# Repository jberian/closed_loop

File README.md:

Closed-Loop System for Type 1 diabetes
====

    This repository contains all the projects needed to build a 
    wearable closed-loop system for type 1 diabetes that uses a new
    algorithm to estimate the basal insulin needs of the patient and
    perform the control using temporary basal rates.

## Disclaimer

    This software and information is designed for educational purposes only 
    and should NEVER be used on real patients.
    
    This information is provided 'as is' and in no event shall the 
    provider be liable for any damages, including, without 
    limitation, damages resulting from lost data or lost profits or 
    revenue, the costs of recovering such data, the costs of substitute 
    data, claims by third parties or for other similar costs, or any 
    special, incidental, or consequential damages arising out of use or
    misuse of this data. The accuracy or reliability of the data is not 
    guaranteed or warranted in any way and the provider disclaim 
    liability of any kind whatsoever, including, without limitation, 
    liability for quality, performance, merchantability and fitness 
    for a particular purpose arising out of the use, or inability 
    to use the data. Information obtained via this software MUST
    NEVER BE USED to take medical decisions.

## [License - GPL V2](gpl-v2)
[gpl-2]: https://www.gnu.org/licenses/old-licenses/gpl-2.0.txt

    This program is free software: you can redistribute it and/or modify
    it under the terms of the GNU General Public License as published by
    the Free Software Foundation version 2 of the License.

    This program is distributed in the hope that it will be useful,
    but WITHOUT ANY WARRANTY; without even the implied warranty of
    MERCHANTABILITY or FITNESS FOR A PARTICULAR PURPOSE.  See the
    GNU General Public License for more details.

    You should have received a copy of the GNU General Public License
    along with this program.  If not, see <http://www.gnu.org/licenses/>.

## Contents

   This repository containts the following information in their corresponding
   folder:
   
1. **Demo** - Contains a time-lapse video of a demo system connected to Nightscout and controlling a patient's glycaemia.

2. **Firmware** - Contains the project files needed to compile the platform's CC1111 firmware using IAR Embedded Workbench (the trial version should be enough). The code for the CC2540 processor is not included since the project should be downloaded directly from TI's website.
   
3. **Platform** - Contains the information to build two different platforms: 
    1. *Prototype* - It's a PCB in which some commercial off-the-self boards can be soldered and provides the needed interconnections for the system.
    2. *Final* - Final version of the wearable system.
 
4. **Publications** - Publications related to this work.

5. **Simulation** - Contains a modified version of the [simglucose simulator](https://github.com/jxx123/simglucose) along with a controller that behaves like the "real" version of the controller.

6. **Uploader** - Contains the xCode project for an really simple iOS uploader for Nightscout. This software allows the platform to upload data to Nightscout using an iOS device.

## Thanks

None of this would be possible without all the hard work of my colleagues Ignacio Bravo, Alfredo Gardel and Jose Luis Lazaro.

Sergio Hernandez, thank you very much for your countless hours of hardware designing.

And thank you Jinyu Xie for developing such excellent software ([simglucose](https://github.com/jxx123/simglucose)) and allow us to build upon it.

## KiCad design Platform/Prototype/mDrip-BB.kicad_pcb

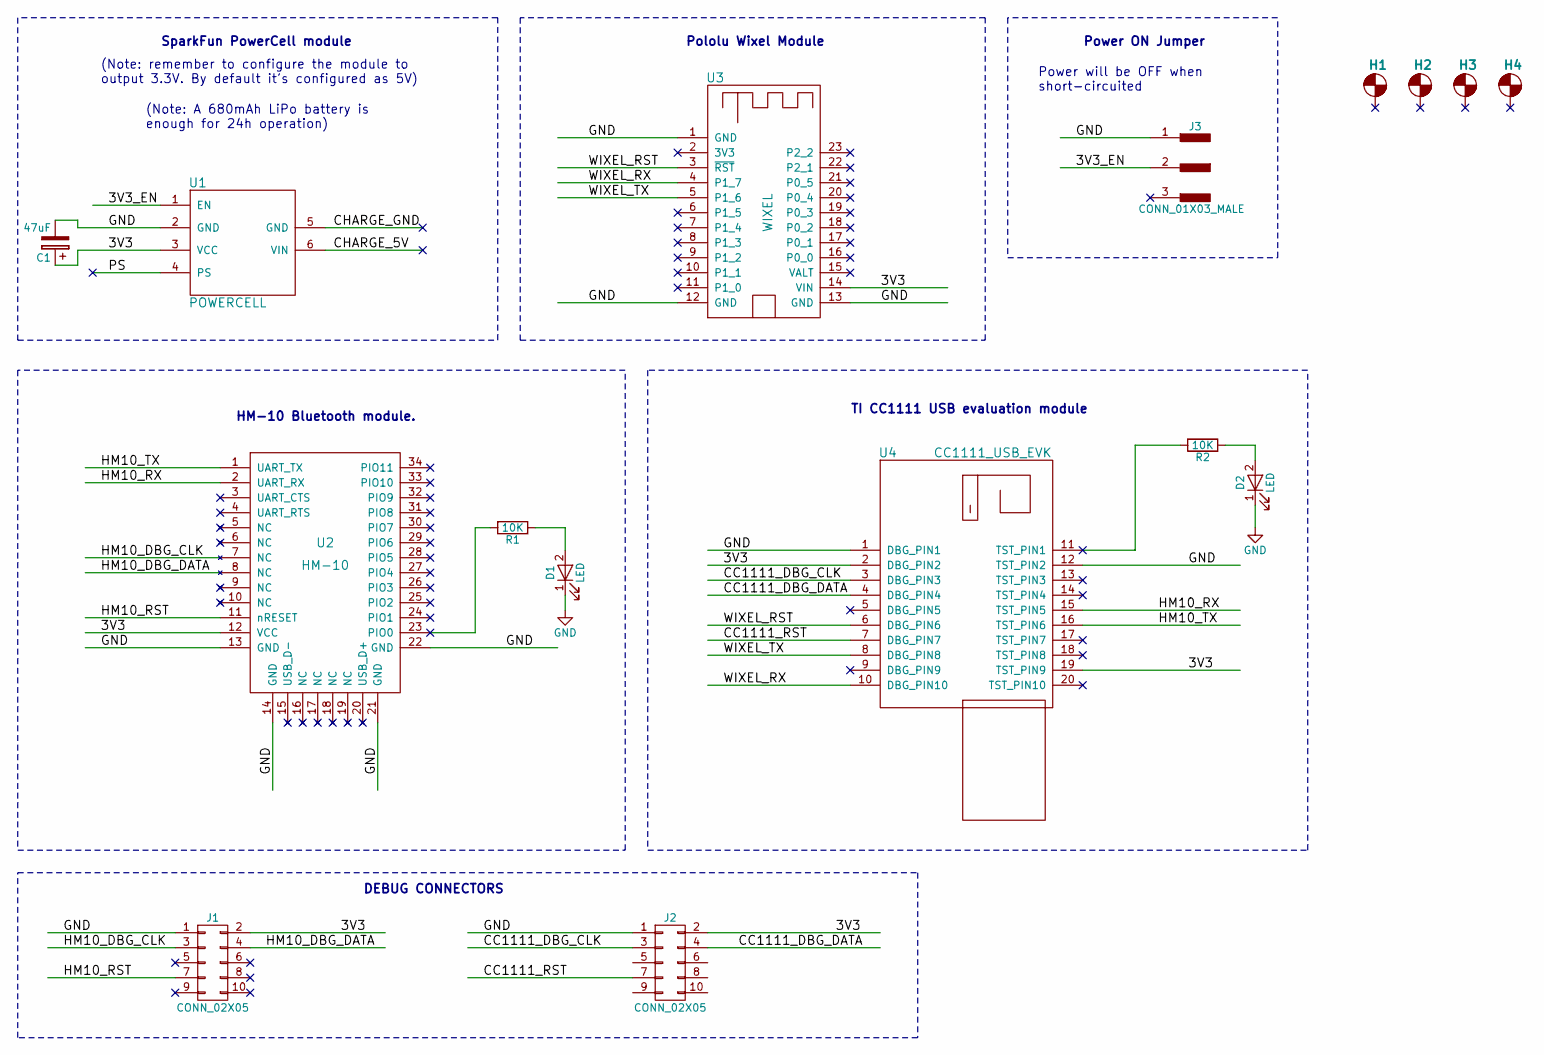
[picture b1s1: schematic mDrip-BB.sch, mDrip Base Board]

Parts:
C1: 47uF; CP_Radial_D5.0mm_P2.50mm
D1, D2: LED; LED_D5.0mm
H1, H2, H3, H4: Hole; MountingHole_2.7mm_M2.5_Pad
J1, J2: CONN_02X05; Pin_Header_Straight_2x05_Pitch2.54mm
J3: CONN_01X03_MALE; Pin_Header_Straight_1x03_Pitch2.54mm
R1, R2: 10K; R_Axial_DIN0204_L3.6mm_D1.6mm_P5.08mm_Horizontal
U1: POWERCELL
U2: HM-10; HM10; MPN HM-10
U3: WIXEL
U4: CC1111_USB_EVK

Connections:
/3V3: C1.1, J1.2, J2.2, U1.3 (VCC), U2.12 (VCC), U3.14 (VIN), U4.2 (DBG_PIN2), U4.19 (TST_PIN9)
/3V3_EN: J3.2, U1.1 (EN)
/CC1111_DBG_CLK: J2.3, U4.3 (DBG_PIN3)
/CC1111_DBG_DATA: J2.4, U4.4 (DBG_PIN4)
/CC1111_RST: J2.7, U4.7 (DBG_PIN7)
/CHARGE_5V: U1.6 (VIN)
/CHARGE_GND: U1.5 (GND)
/HM10_DBG_CLK: J1.3, U2.7 (NC)
/HM10_DBG_DATA: J1.4, U2.8 (NC)
/HM10_RST: J1.7, U2.11 (nRESET)
/HM10_RX: U2.2 (UART_RX), U4.15 (TST_PIN5)
/HM10_TX: U2.1 (UART_TX), U4.16 (TST_PIN6)
/PS: U1.4 (PS)
/WIXEL_RST: U3.3 (~RST), U4.6 (DBG_PIN6)
/WIXEL_RX: U3.4 (P1_7), U4.10 (DBG_PIN10)
/WIXEL_TX: U3.5 (P1_6), U4.8 (DBG_PIN8)
GND: C1.2, D1.1 (K), D2.1 (K), J1.1, J2.1, J3.1, U1.2 (GND), U2.13 (GND), U2.14 (GND), U2.21 (GND), U2.22 (GND), U3.1 (GND), U3.12 (GND), U3.13 (GND), U4.1 (DBG_PIN1), U4.12 (TST_PIN2)
unnamed: D1.2 (A), R1.1
unnamed: D2.2 (A), R2.1
unnamed: R1.2, U2.23 (PIO0)
unnamed: R2.2, U4.11 (TST_PIN1)

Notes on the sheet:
HM-10 Bluetooth module.
Power ON Jumper
Power will be OFF when short-circuited
SparkFun PowerCell module
(Note: remember to configure the module to output 3.3V. By default it's configured as 5V)
(Note: A 680mAh LiPo battery is enough for 24h operation)
DEBUG CONNECTORS
Pololu Wixel Module
TI CC1111 USB evaluation module

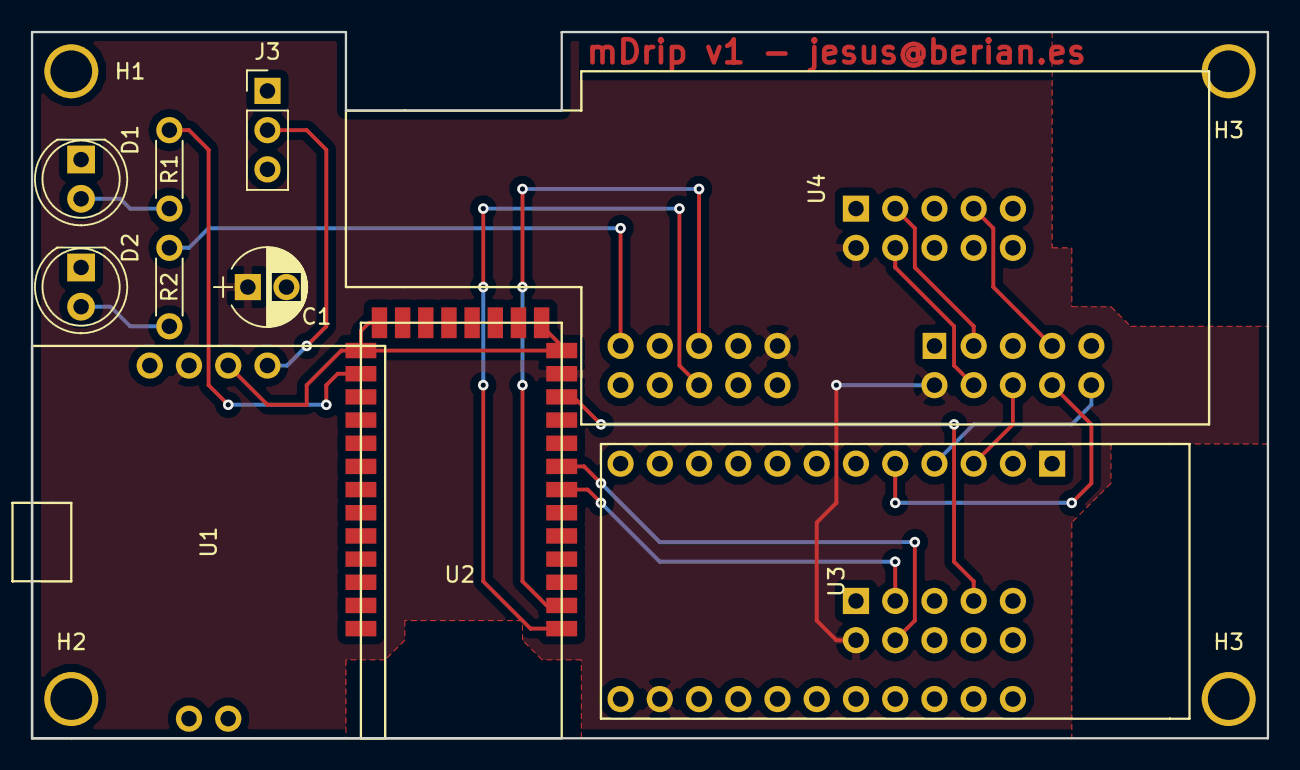
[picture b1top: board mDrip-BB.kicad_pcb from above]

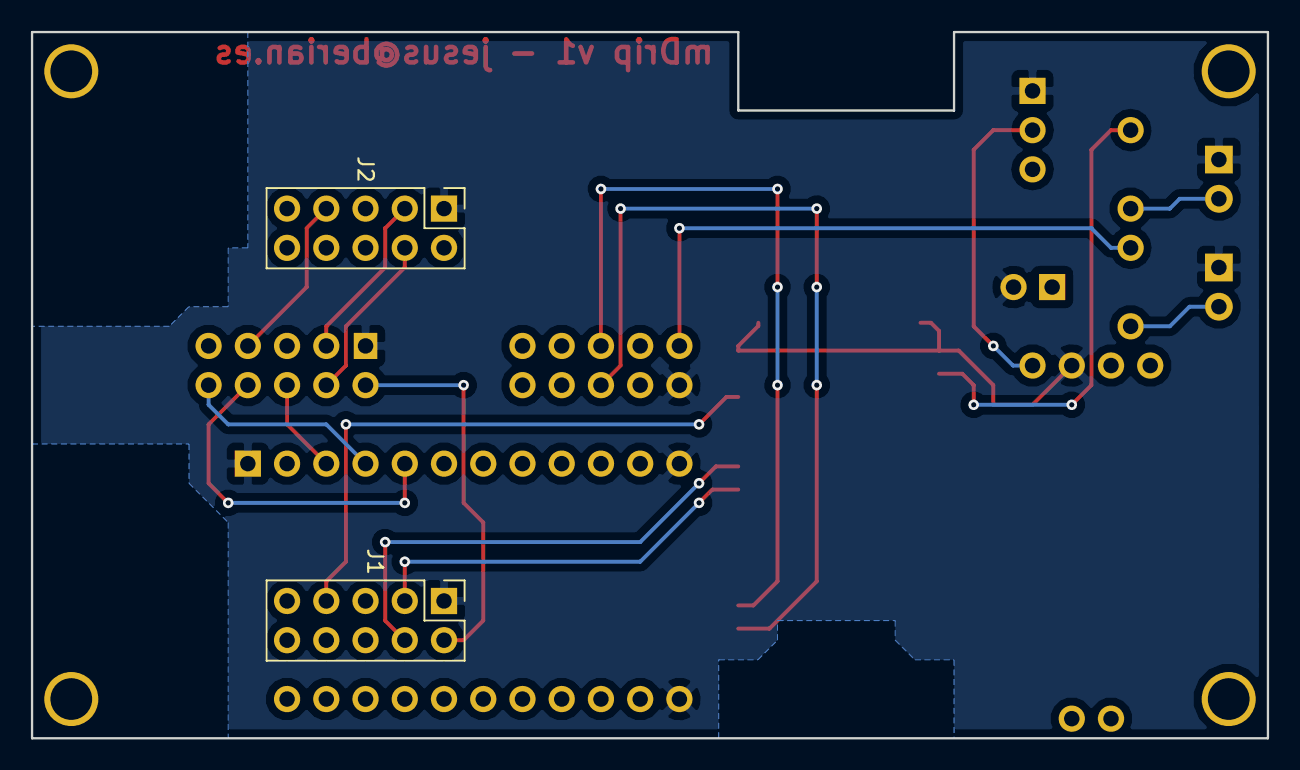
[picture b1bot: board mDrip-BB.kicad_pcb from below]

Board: 2 copper layers, 80.0 x 45.7 mm, 16 parts (2 on the bottom side), 18 nets.

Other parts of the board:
H3#2: MountingHole_2.7mm_M2.5_Pad

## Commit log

2020-11-20 First upload
